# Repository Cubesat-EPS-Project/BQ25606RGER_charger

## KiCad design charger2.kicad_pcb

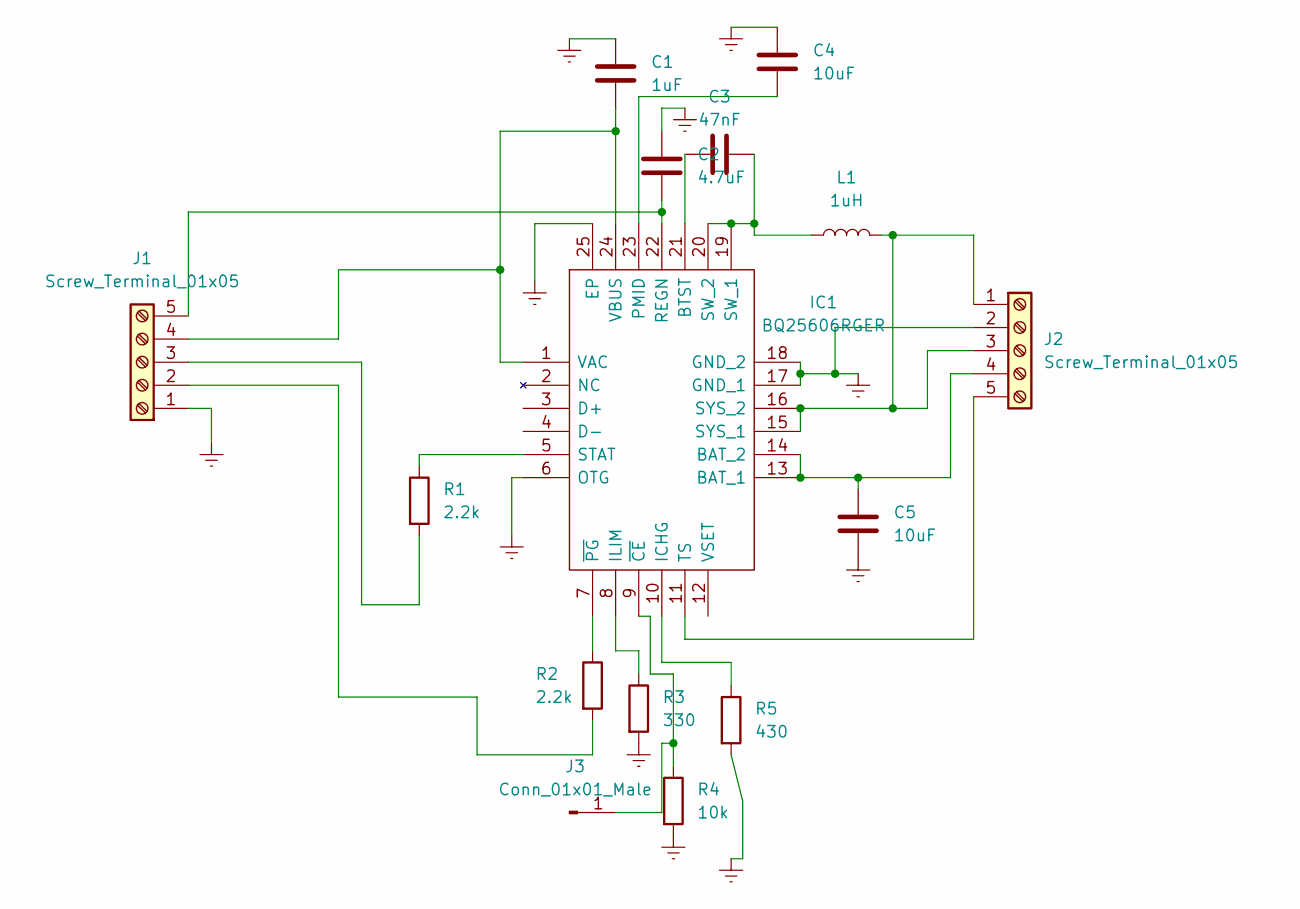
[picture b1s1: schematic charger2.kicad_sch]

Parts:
C1: 1uF; C1206
C2: 4.7uF; C1210
C3: 47nF; C1005_Commercial
C4, C5: 10uF; CAPC2012X94N
IC1: BQ25606RGER; QFN50P400X400X100-25N-D; Mouser Part Number 595-BQ25606RGER
J1, J2: Screw_Terminal_01x05; TerminalBlock_MetzConnect_Type059_RT06305HBWC_1x05_P3.50mm_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
J3: Conn_01x01_Male; PinHeader_1x01_P1.00mm_Vertical
L1: 1uH; IHHP0805ZHER1R0M01
R1, R2: 2.2k; RESC2012X65N
R3: 330; H2C_H2R
R4: 10k; ERA8KEB1004V
R5: 430; ERJH3

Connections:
Earth: C1.1, C2.1, C4.1, C5.2, IC1.6 (OTG), IC1.17 (GND_1), IC1.18 (GND_2), IC1.25 (EP), J1.1, J2.2, R3.2, R4.2, R5.2
unnamed: C1.2, IC1.1 (VAC), IC1.24 (VBUS), J1.4
unnamed: C2.2, IC1.22 (REGN), J1.5
unnamed: C3.1, IC1.21 (BTST)
unnamed: C3.2, IC1.19 (SW_1), IC1.20 (SW_2), L1.1
unnamed: C4.2, IC1.23 (PMID)
unnamed: C5.1, IC1.13 (BAT_1), IC1.14 (BAT_2), J2.4
unnamed: IC1.5 (STAT), R1.1
unnamed: IC1.7 (~PG), R2.1
unnamed: IC1.8 (ILIM), R3.1
unnamed: IC1.9 (~CE), J3.1, R4.1
unnamed: IC1.10 (ICHG), R5.1
unnamed: IC1.11 (TS), J2.5
unnamed: IC1.15 (SYS_1), IC1.16 (SYS_2), J2.1, J2.3, L1.2
unnamed: J1.3, R1.2
unnamed: J1.2, R2.2

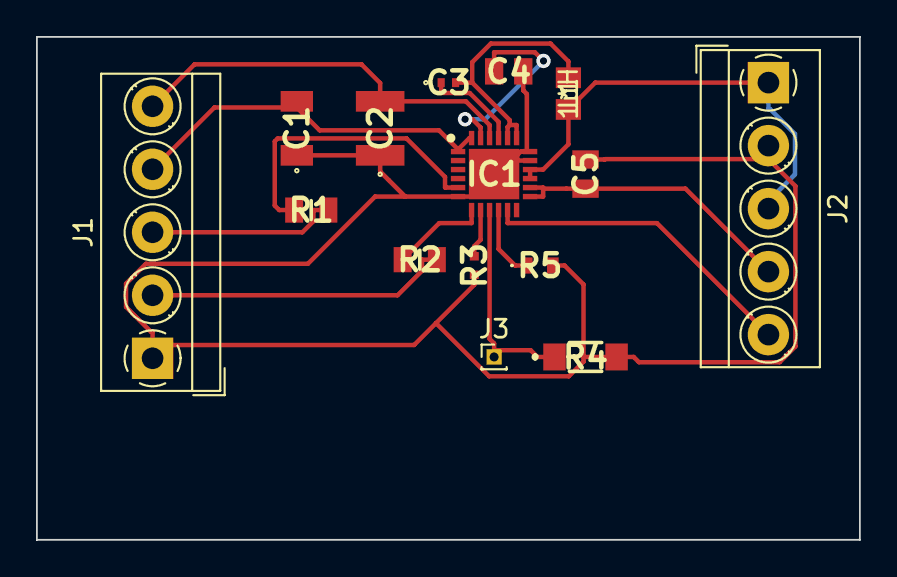
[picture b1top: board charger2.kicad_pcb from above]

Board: 2 copper layers, 45.7 x 27.9 mm, 15 parts (0 on the bottom side), 16 nets.

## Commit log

2023-02-11 INIT
2023-02-11 Schematic done
2023-02-11 Libs and 3d export
2023-02-11 autorouted
2023-02-22 patch

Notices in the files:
parts and their libraries:
Copyright 2021 Accelerated Designs. All rights reserved.
